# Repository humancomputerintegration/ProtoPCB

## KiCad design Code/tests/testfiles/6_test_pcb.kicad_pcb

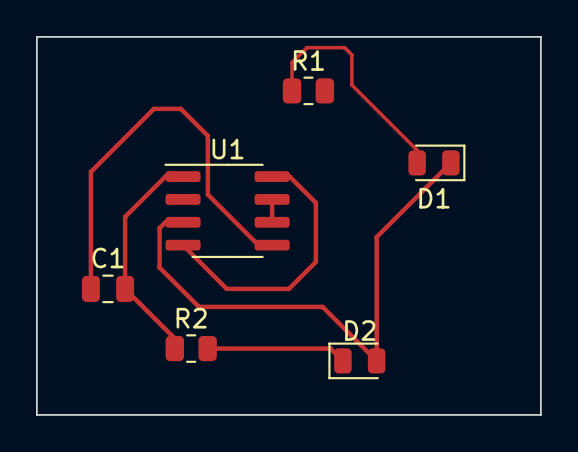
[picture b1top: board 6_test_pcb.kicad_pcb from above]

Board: 2 copper layers, 28.0 x 21.0 mm, 6 parts (0 on the bottom side), 7 nets.

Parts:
C1: C; C_0805_2012Metric
D1, D2: LED; LED_0805_2012Metric
R1, R2: R; R_0805_2012Metric
U1: LM555xM; SOIC-8_3.9x4.9mm_P1.27mm

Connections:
GND: C1.2, R2.1, U1.1 (GND)
unnamed: D1.2 (A), R1.1
unnamed: D1.1 (K), D2.2 (A), U1.3 (Q)
unnamed: D2.1 (K), R2.2
unnamed: C1.1, U1.5 (CV)
unnamed: U1.6 (THR), U1.7 (DIS)
VCC: R1.2, U1.4 (R), U1.8 (VCC)

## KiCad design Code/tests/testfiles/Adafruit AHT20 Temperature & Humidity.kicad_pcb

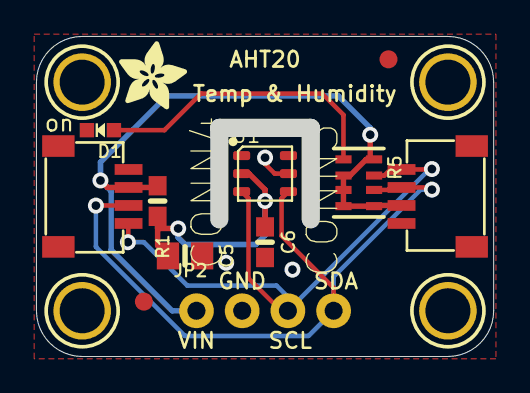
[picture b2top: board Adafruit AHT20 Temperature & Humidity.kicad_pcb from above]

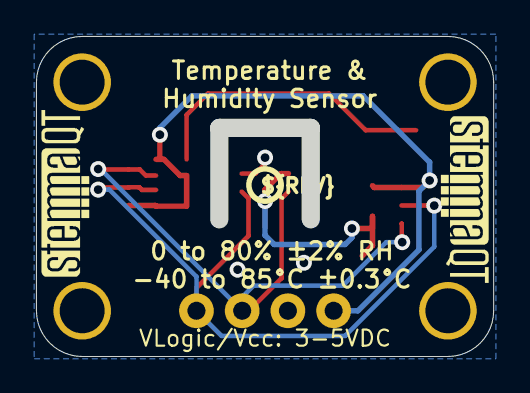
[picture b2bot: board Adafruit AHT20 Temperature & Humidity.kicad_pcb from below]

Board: 2 copper layers, 25.4 x 17.8 mm, 19 parts (3 on the bottom side), 6 nets.

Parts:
C5: 10uF; 0805-NO
C6: 0.1uF; 0603-NO
CONN3, CONN4: STEMMA_I2C_QT; JST_SH4
D1: GREEN; CHIPLED_0603_NOOUTLINE
FID3, FID4: FIDUCIAL_1MM
JP2: 1X04_ROUND_76
R1: 220; 0603-NO
R5: 10K; RESPACK_4X0603
U1: AHT20; SNR6-1.0-3X3X1MM
U$19, U$20, U$22, U$25: MOUNTINGHOLE2.5; MOUNTINGHOLE_2.5_PLATED
U$28: ADAFRUIT_3.5MM
U$29: PCBFEAT-REV-040
U$30, U$31: STEMMAQT

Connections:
GND: C5.2, C6.2, CONN3.1, CONN3.MT1, CONN3.MT2, CONN4.1, CONN4.MT1, CONN4.MT2, D1.C, JP2.2, U1.5
unnamed: D1.A, R5.1
SCL: CONN3.4, CONN4.4, JP2.3, R5.7, U1.3
SDA: CONN3.3, CONN4.3, JP2.4, R5.6, U1.4
VCC: CONN3.2, CONN4.2, JP2.1, R1.1, R5.2, R5.3, R5.4, R5.5, R5.8
VDD: C5.1, C6.1, R1.2, U1.2

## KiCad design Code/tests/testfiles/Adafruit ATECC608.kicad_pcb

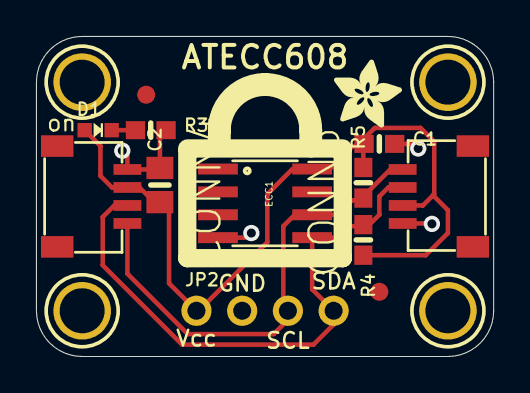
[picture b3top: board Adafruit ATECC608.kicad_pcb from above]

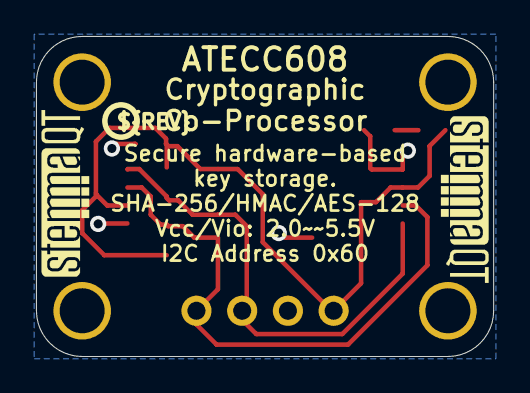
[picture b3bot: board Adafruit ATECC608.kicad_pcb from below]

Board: 2 copper layers, 25.4 x 17.8 mm, 20 parts (3 on the bottom side), 5 nets.

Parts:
C1: 0.1uF; 0603-NO
C2: 10uF; 0805-NO
CONN3, CONN4: STEMMA_I2C_QT; JST_SH4
D1: GREEN; CHIPLED_0603_NOOUTLINE
ECC1: ATECC608; SOIC8
FID3, FID4: FIDUCIAL_1MM
JP2: 1X04_ROUND
R3: 4.7K; 0603-NO
R4, R5: 10K; 0603-NO
U$11, U$12, U$14, U$15: MOUNTINGHOLE2.5; MOUNTINGHOLE_2.5_PLATED
U$17: ADAFRUIT_3.5MM
U$18: PCBFEAT-REV-040
U$19, U$20: STEMMAQT

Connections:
GND: C1.2, C2.2, CONN3.1, CONN4.1, ECC1.4, JP2.2, R3.2
unnamed: D1.C, R3.1
SCL: CONN3.4, CONN4.4, ECC1.6, JP2.3, R5.1
SDA: CONN3.3, CONN4.3, ECC1.5, JP2.4, R4.1
VCC: C1.1, C2.1, CONN3.2, CONN4.2, D1.A, ECC1.8, JP2.1, R4.2, R5.2

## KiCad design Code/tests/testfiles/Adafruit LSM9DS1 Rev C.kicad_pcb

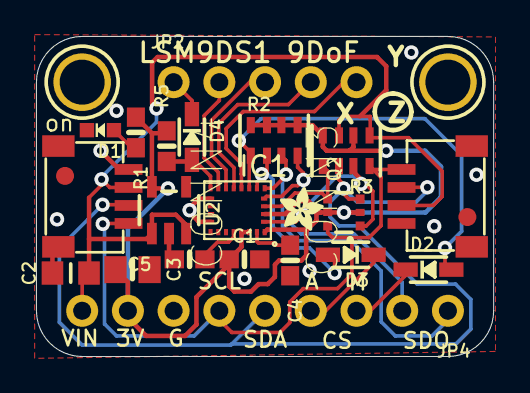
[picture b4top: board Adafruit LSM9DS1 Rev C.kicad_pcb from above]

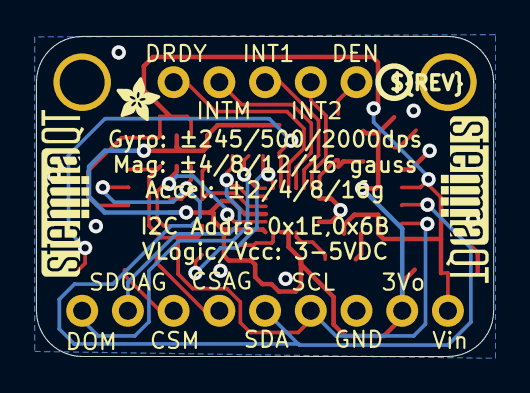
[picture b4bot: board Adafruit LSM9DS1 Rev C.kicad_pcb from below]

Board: 2 copper layers, 25.4 x 17.8 mm, 29 parts (4 on the bottom side), 22 nets.

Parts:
C1: 0.1uF; 0603-NO
C2: 10uF; _0805MP
C3: 10uF; 0805-NO
C4: 0.22uF; 0603-NO
C5: 0.01uF; 0603-NO
CONN3, CONN4: STEMMA_I2C_QT; JST_SH4
D1: GREEN; CHIPLED_0603_NOOUTLINE
D2, D3, D4: 1N4148; SOD-323
FID3, FID4: FIDUCIAL_1MM
IC1: LSM9DS1; LGA24_3.5X3.1MM
JP2: 1X05_ROUND_70
JP4: PowerIO; 1X09_ROUND_70
Q2: BSS138; SOT363
R1, R5: 10K; 0603-NO
R2: 10k; RESPACK_4X0603
R3: 10K; RESPACK_4X0603
U2: AP2112K-3.3; SOT23-5
U$1, U$17: MOUNTINGHOLE2.5; MOUNTINGHOLE_2.5_PLATED
U$10, U$16: ADAFRUIT_2.5MM
U$25: PCBFEAT-REV-040
U$30, U$31: STEMMAQT

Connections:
3.3V: C1.1, C3.1, IC1.1, IC1.3, IC1.22, IC1.23, JP4.8, Q2.2, Q2.5, R1.1, R2.5, R2.6, R2.7, R2.8, R3.2, R3.4, R5.2, U2.5
C1: C4.1, IC1.24
CAP: C5.1, IC1.21
CS_A/G: D3.A, IC1.7, R2.2
CS_AG_5V: D3.C, JP4.4
CS_M: D2.A, IC1.8, R2.1
CS_M_5V: D2.C, JP4.3
DEN_3V: D4.A, IC1.13, R5.1
DEN_5V: D4.C, JP2.1
DRDY_M: IC1.9, JP2.5
GND: C1.2, C2.2, C3.2, C4.2, C5.2, CONN3.1, CONN3.MT1, CONN3.MT2, CONN4.1, CONN4.MT1, CONN4.MT2, D1.C, IC1.14, IC1.15, IC1.16, IC1.17, IC1.18, IC1.19, IC1.20, JP4.7, U2.2
INT1_AG: IC1.11, JP2.3
INT2_AG: IC1.12, JP2.2
INT_M: IC1.10, JP2.4
unnamed: D1.A, R1.2
SCL: CONN3.4, CONN4.4, JP4.6, Q2.6, R3.8
SCL_3V: IC1.2, Q2.1, R3.7
SDA: CONN3.3, CONN4.3, JP4.5, Q2.3, R3.6
SDA_3V: IC1.4, Q2.4, R3.5
SDO_AG: IC1.5, JP4.2, R2.4
SDO_M: IC1.6, JP4.1, R2.3
VCC: C2.1, CONN3.2, CONN4.2, JP4.9, R3.1, R3.3, U2.1, U2.3

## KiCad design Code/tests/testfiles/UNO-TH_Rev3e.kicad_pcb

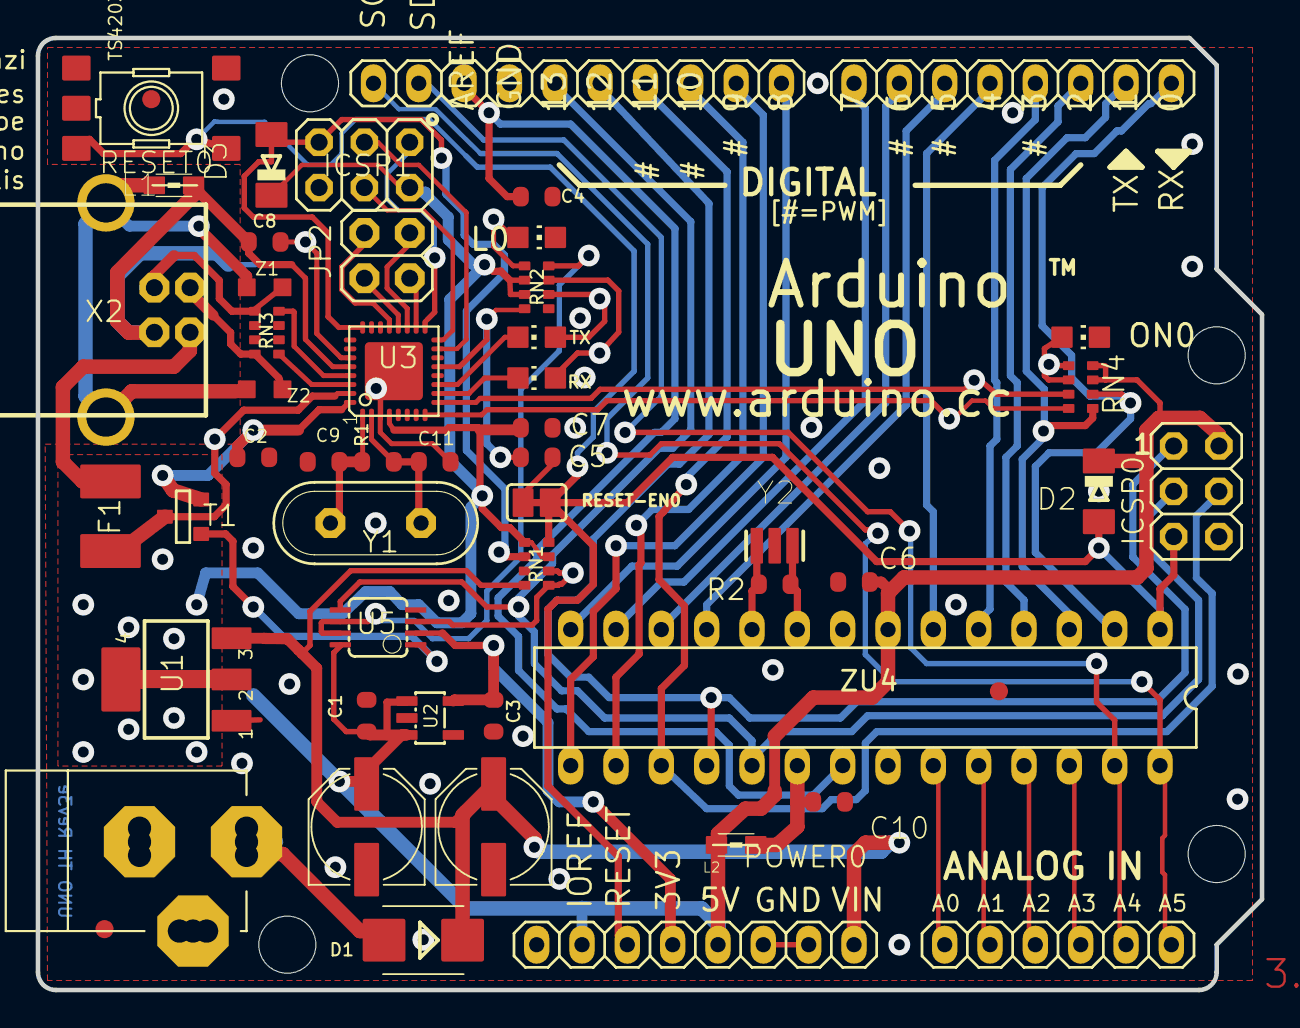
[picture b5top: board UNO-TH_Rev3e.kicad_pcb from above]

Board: 2 copper layers, 68.6 x 53.3 mm, 119 parts (1 on the bottom side), 61 nets.

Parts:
@HOLE0, @HOLE1, @HOLE2, @HOLE3: (no value)
AD0: 6x1F-H8.5; 1X06
C1, C2, C4, C5, C6, C7, C10: 100n; C0603-ROUND
C3, C8: 1u; C0603-ROUND
C9, C11: 22p; C0603-ROUND
D1: M7; SMB
D2, D3: CD1206-S01575; MINIMELF
F1: MF-MSMF050-2 500mA; L1812
FD1, FD2, FD3: FIDUCIALMOUNT; FIDUCIA-MOUNT
GND_TP0, GND_TP1: TP_SP; TP-SP
GROUND0: SJ
ICSP0, ICSP1: 3x2 M; 2X03
IOH0: 10x1F-H8.5; 1X10
IOL0: 8x1F-H8.5; 1X08
JP2: 2x2 M - NM; 2X02
L0: YELLOW; CHIP-LED0805
L1: BLM21; 0805
L2: 10uH; 0805
ON0: GREEN; CHIP-LED0805
ORIGIN0: TP_SP; TP-SP
PC1, PC2: 47u; PANASONIC_D
POWER0: 8x1F-H8.5; 1X08
R1, R2: 1M; R0603-ROUND
RESET0: TS42031-160R-TR-7260; TS42
RESET-EN0: SJ
RN1: 10K; CAY16
RN2, RN4: 1K; CAY16
RN3: 22R; CAY16
RX0: YELLOW; CHIP-LED0805
T1: FDN340P; SOT-23
TP_0, TP_1, TP_2, TP_3, TP_3V3, TP_4, TP_5, TP_5V0, TP_5V1, TP_6, TP_7, TP_8, TP_9, TP_10, TP_11, TP_12, TP_13: TP_SP; TP-SP
TP_A0, TP_A1, TP_A2, TP_A3, TP_A4, TP_A5: TP_SP; TP-SP
TP_AREF0: TP_SP; TP-SP
TP_CMP0: TP_SP; TP-SP
TP_D+0: TP_SP; TP-SP
TP_D-0: TP_SP; TP-SP
TP_DTR0: TP_SP; TP-SP
TP_GATE0: TP_SP; TP-SP
TP_LCMD0: TP_SP; TP-SP
TP_LL0: TP_SP; TP-SP
TP_MISO2: TP_SP; TP-SP
TP_MOSI2: TP_SP; TP-SP
TP_ONL0: TP_SP; TP-SP
TP_PB4, TP_PB5, TP_PB6, TP_PB7: TP_SP; TP-SP
TP_PWRIN0: TP_SP; TP-SP
TP_RESET0, TP_RESET2: TP_SP; TP-SP
TP_RX0: TP_SP; TP-SP
TP_RXL0: TP_SP; TP-SP
TP_SCK2: TP_SP; TP-SP
TP_SCL0: TP_SP; TP-SP
TP_SDA0: TP_SP; TP-SP
TP_TX0: TP_SP; TP-SP
TP_TXL0: TP_SP; TP-SP
TP_UGND0: TP_SP; TP-SP
TP_USBVCC0: TP_SP; TP-SP
TP_USH0: TP_SP; TP-SP
TP_VIN0: TP_SP; TP-SP
TP_VUCAP0: TP_SP; TP-SP
TP_XT1, TP_XT2, TP_XT3, TP_XT4: TP_SP; TP-SP
TP_XUSB0: TP_SP; TP-SP
TX0: YELLOW; CHIP-LED0805
U1: NCP1117ST50T3G; SOT223
U2: LP2985-33DBVR; SOT23-DBV
U3: ATMEGA16U2-MU(R); MLF32
U5: LMV358IDGKR; MSOP08
X1: POWERSUPPLY_DC21MMX; POWERSUPPLY_DC-21MM
X2: USB-B_TH; PN61729
Y1: 16MHz; QS
Y2: CSTCE16M0V53-R0 16MHZ; RESONATOR
Z1, Z2: CG0603MLC-05E; CT_CN0603
ZU4: ATMEGA328P-PU; DIL28-3

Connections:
+3V3: C3.2, POWER0.4, TP_3V3.X, U2.5, U5.2
+5V: C1.2, C2.2, C6.2, C7.1, D2.C, D3.C, ICSP0.2, ICSP1.2, L2.1, PC2.+, POWER0.2, POWER0.5, RN1.3, RN1.5, RN2.2, RN2.3, RN4.3, RN4.4, T1.2, TP_5V0.X, TP_5V1.X, U1.2, U1.4, U2.1, U2.3, U3.4, U3.32, U5.8, ZU4.7
AD0: AD0.1, TP_A0.X, ZU4.23
AD1: AD0.2, TP_A1.X, ZU4.24
AD2: AD0.3, TP_A2.X, ZU4.25
AD3: AD0.4, TP_A3.X, ZU4.26
AD4/SDA: AD0.5, IOH0.9, TP_A4.X, TP_SDA0.X, ZU4.27
AD5/SCL: AD0.6, IOH0.10, TP_A5.X, TP_SCL0.X, ZU4.28
AREF: C4.2, IOH0.8, TP_AREF0.X, ZU4.21
AVCC: C10.2, L2.2, ZU4.20
CMP: RN1.1, RN1.2, TP_CMP0.X, U5.3
D+: RN3.5, TP_D+0.X, X2.3, Z1.1
D-: RN3.8, TP_D-0.X, X2.2, Z2.1
DTR: C5.1, RN2.4, TP_DTR0.X, U3.13
GATE_CMD: T1.3, TP_GATE0.X, U5.1
GND: C1.1, C2.1, C3.1, C4.1, C6.1, C7.2, C9.2, C10.1, C11.2, GND_TP0.X, GND_TP1.X, GROUND0.1, ICSP0.6, ICSP1.6, IOH0.7, L0.C, ON0.C, PC1.-, PC2.-, POWER0.6, POWER0.7, RESET0.1, RESET0.2, RN1.7, RN2.5, U1.1, U2.2, U3.3, U3.33, U5.4, X1.1, X1.3, Y2.2, ZU4.8, ZU4.22
IO0: IOL0.1, RN4.2, TP_0.X, ZU4.2
IO1: IOL0.2, RN4.1, TP_1.X, ZU4.3
IO2: IOL0.3, TP_2.X, ZU4.4
IO3: IOL0.4, TP_3.X, ZU4.5
IO4: IOL0.5, TP_4.X, ZU4.6
IO5: IOL0.6, TP_5.X, ZU4.11
IO6: IOL0.7, TP_6.X, ZU4.12
IO7: IOL0.8, TP_7.X, ZU4.13
IO8: IOH0.1, TP_8.X, ZU4.14
IO9: IOH0.2, TP_9.X, ZU4.15
L13: RN2.8, TP_LCMD0.X, U5.6, U5.7
M8RXD: RN4.7, TP_RX0.X, U3.9
M8TXD: RN4.8, TP_TX0.X, U3.8
MISO: ICSP0.1, IOH0.5, TP_12.X, ZU4.18
MISO2: ICSP1.1, TP_MISO2.X, U3.17
MOSI: ICSP0.4, IOH0.4, TP_11.X, ZU4.17
MOSI2: ICSP1.4, TP_MOSI2.X, U3.16
unnamed: L0.A, RN2.1, TP_LL0.X
unnamed: ON0.A, RN4.5, RN4.6, TP_ONL0.X
unnamed: RN2.7, RX0.A, TP_RXL0.X
unnamed: RN2.6, TP_TXL0.X, TX0.A
PB4: JP2.1, TP_PB4.X, U3.18
PB5: JP2.3, TP_PB5.X, U3.19
PB6: JP2.2, TP_PB6.X, U3.20
PB7: JP2.4, TP_PB7.X, U3.21
PWRIN: D1.A, TP_PWRIN0.X, X1.2
RD+: RN3.4, U3.29
RD-: RN3.1, U3.30
RESET: C5.2, D2.A, ICSP0.5, POWER0.3, RESET0.3, RESET0.4, RESET-EN0.1, RESET-EN0.2, RN1.4, TP_RESET0.X, ZU4.1
RESET2: D3.A, ICSP1.5, RN1.6, TP_RESET2.X, U3.24
RXLED: RX0.C, U3.10
SCK: ICSP0.3, IOH0.6, TP_13.X, U5.5, ZU4.19
SCK2: ICSP1.3, TP_SCK2.X, U3.15
SS: IOH0.3, TP_10.X, ZU4.16
TP_VUCAP: C8.1, TP_VUCAP0.X, U3.27
TXLED: TX0.C, U3.11
UGND: C8.2, GROUND0.2, L1.1, TP_UGND0.X, U3.28, X2.4
USBVCC: F1.1, T1.1, TP_USBVCC0.X, U3.31
USHIELD: L1.2, TP_USH0.X, X2.P$1, X2.P$2, Z1.2, Z2.2
VIN: D1.C, PC1.+, POWER0.8, RN1.8, TP_VIN0.X, U1.3
XT1: C9.1, R1.1, TP_XT3.X, U3.1, Y1.2
XT2: C11.1, R1.2, TP_XT4.X, U3.2, Y1.1
XTAL1: R2.1, TP_XT1.X, Y2.3, ZU4.9
XTAL2: R2.2, TP_XT2.X, Y2.1, ZU4.10
XUSB: F1.2, TP_XUSB0.X, X2.1
